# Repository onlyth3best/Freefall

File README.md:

# Freefall
a PCB with an accelerometer… (built with help from https://hermes.hackclub.com/!)
<br/> About the folders: /code has all the code, /prod has all the production files!
<br/> 3d models are in pcb/3dmodels
<br/>
<br/>
The idea is, each LED is linked to a specific direction. For example, left is the first LED, up is the second LED and so on. By 'entering' a the directions into the PCB, you find the combination of directions that make up a certain code!
<br/> note: PCB models are in pcb/kicad! other 3D models that were used were not sourced by me :)
<br/>
<br/> The motivation for this project was mainly to work more on my PCB skills, as well as my ability to read through documentation of a component and get the addresses right. I think that adding the 'code' feature with the lights was also a fun thing I just wanted to add.
<br/>
In terms of code, I haven't fully done the firmware as I don't have the actual thing yet, but here's a guide for setting up the XIAO_RP2040 with Arduino: https://wiki.seeedstudio.com/XIAO-RP2040-with-Arduino/
The firmware I've added is in progress as of now (26/04/26) and I will add setup steps in the future, when I have the physical PCB itself.
<br/>
<br/> image of PCB:
<br/>

## setup:
Connect to the XIAO, using the Arduino IDE
-This link might help: https://wiki.seeedstudio.com/XIAO-RP2040-with-Arduino/
-The code should work… once I've finished polishing it (not completely done as of now…)

## schematics:
<br/>

<br/> pcb editor/wiring:
<br/>
<
<br/>
<br/>
# Setup:
<br/> Wiring:
<br/>LED1 = D0
<br/>LED2 = D1
<br/>LED3 = D2
<br/>LED4 = D3
<br/>Accelerometer & Screen = [various, see schematics]
<br/> Cap1 = C1
<br/> Cap2 = C2

<br/>
# Assembly instructions, for now:
<br/>~ Solder these things onto the PCB, according to the schematics:
<br/>~ - XIAO_RP_2040
<br/>~ - four LEDs
<br/>~ - four resistors
<br/>~ - OLED screen
<br/>~ - Accelerometer
<br/>~ - two capacitors
<br/>~ After this, connect the board to the power, this link could help: https://wiki.seeedstudio.com/XIAO-RP2040-with-Arduino/

<br/>also Flash instructions:
<br/> - install ArduinoIDE, https://docs.arduino.cc/software/ide/
<br/> - add the support for the RP2040 (Preferences > Additional Board Manager URLs > "https://github.com/earlephilhower/arduino-pico/releases/download/global/package_rp2040_index.json")
<br/> - connect the XIAO RP_2040 via USB
<br/> - upload the code from this repo in /firmware!

<br/>

[frefallzine.pdf](https://github.com/user-attachments/files/29169083/frefaline.pdf)

<br/>
<br/>
PCB BOM:
<br/>
<br/>
<br/>

| Designator         | Footprint         | Quantity | Approx. Price (USD) | Part / Designation | Link |
|--------------------|-------------------|----------|---------------------|--------------------|------|
| D1, D2, D3, D4 | LEDRD254W57L (LEDs) | 4 | $3.90               | L08R5000Q1         | https://jlcpcb.com/parts/2nd/Optoelectronics/LED_Indication_Discrete_71 |
| DS1                | LCD_OLED_128 (OLED screen) | 1 | $0.10               | OLED_128X64        | https://thepihut.com/products/1-3-oled-display-module-128x64 |
| R1, R2, R3, R4 | R_Axial_DIN020 (resistors) | 4 | $0.01               | R                  | https://jlcpcb.com/parts/1st/Resistors_1 |
| U1                 | PQFN50P300X3 (accelerometer) | 1 | $7.20               | MMA8452QR1         | https://www.mouser.co.uk/ProductDetail/STMicroelectronics/MMA8452QR1 |
| U2                 | XIAO-RP2040-D | 1        | $4.80 | XIAO-RP2040-D      | https://www.seeedstudio.com/XIAO-RP2040-v1-0-p-5026.html |
| C1, C2                 | Capacitor_THT:CP_Radial_D5.0mm_P2.00mm | 2        | $0.01 | C      | https://jlcpcb.com/partdetail/1876-0402B103K500NT/C1524 |
| - | - | - | total ~ 16.03 | - | - |

<br/> planning to source from JLCPCB (apologies if the BOM is wrong, I'm new to this)

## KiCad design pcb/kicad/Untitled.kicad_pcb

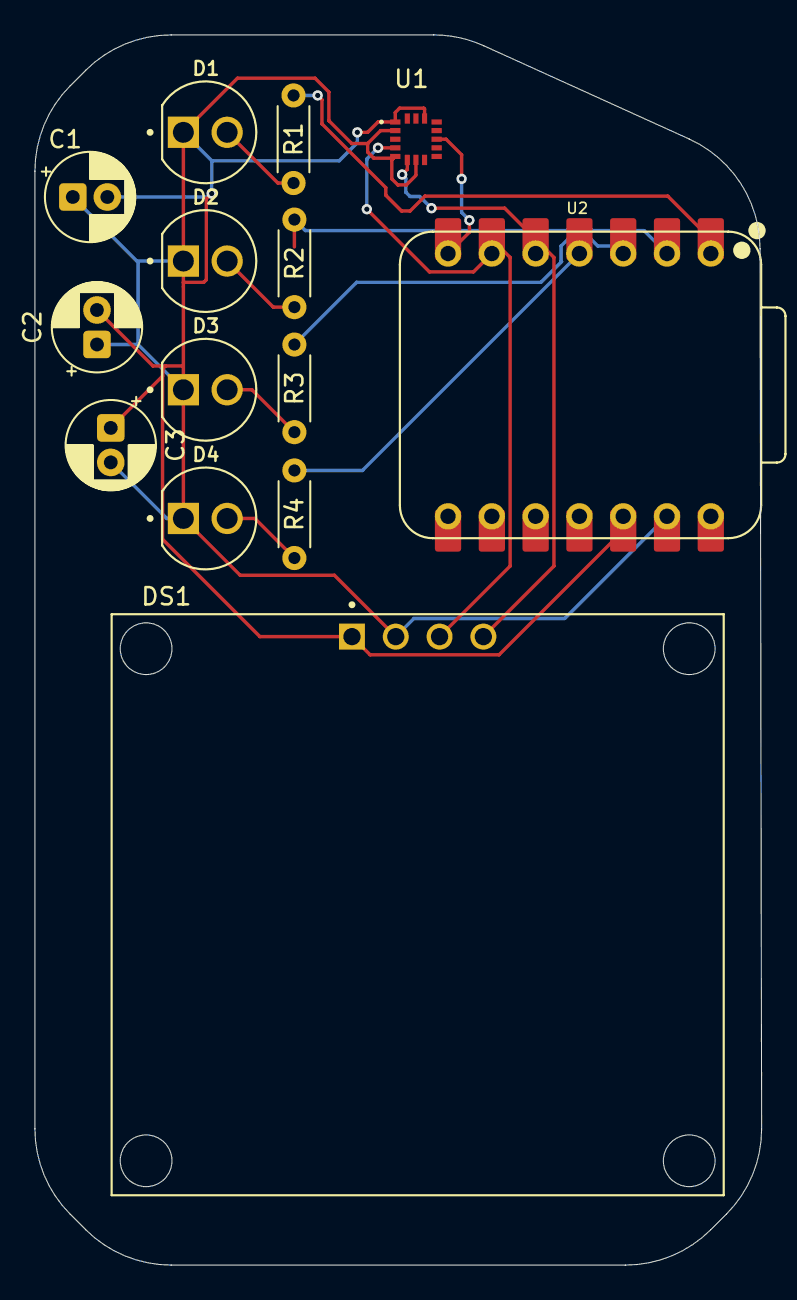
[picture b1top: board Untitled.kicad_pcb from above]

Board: 2 copper layers, 42.1 x 71.4 mm, 14 parts (0 on the bottom side), 13 nets.

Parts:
C1, C2: 0.1uF; CP_Radial_D5.0mm_P2.00mm
C3: 4.7uF; CP_Radial_D5.0mm_P2.00mm
D1, D2, D3, D4: L08R5000Q1; LEDRD254W57D500H1070
DS1: OLED_128X64_1.3_I2C; LCD_OLED_128X64_1.3_I2C
R1, R2, R3, R4: R; R_Axial_DIN0204_L3.6mm_D1.6mm_P5.08mm_Horizontal
U1: MMA8452QR1; PQFN50P300X300X100-16N
U2: XIAO-RP2040-DIP

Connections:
3.3V: C1.2, C2.2, C3.1, DS1.1 (VDD), U1.1 (VDDIO), U1.14 (VDD), U2.12 (3V3)
GND: C1.1, C2.1, C3.2, D1.C, D2.C, D3.C, D4.C, DS1.2 (GND), U1.2 (BYP), U1.5 (GND), U1.7 (SA0), U2.13 (GND)
INTERRUPT: U1.11 (INT1), U2.7 (P0_D6_TX)
LED1: R1.2, U2.1 (P26_A0_D0)
LED2: R2.2, U2.2 (P27_A1_D1)
LED3: R3.2, U2.3 (P28_A2_D2)
LED4: R4.2, U2.4 (P29_A3_D3)
unnamed: D1.A, R1.1
unnamed: D2.A, R2.1
unnamed: D3.A, R3.1
unnamed: D4.A, R4.1
SCL: DS1.3 (SCK), U1.4 (SCL), U2.6 (P7_SCL_D5)
SDA: DS1.4 (SDA), U1.6 (SDA), U2.5 (P6_SDA_D4)

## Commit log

2026-04-24 Create test
2026-06-21 Create prod
